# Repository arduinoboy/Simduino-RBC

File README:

Simduino RBC
-------------------
The object of this project is to create
a Arduino compatible robot controller using a minimum 
of parts.
-------------------
Bootloader
-------------------
The Simduino RBC uses the USBaspLoader
http://www.obdev.at/products/vusb/usbasploader.html
which uses a software only USB driver to connect to the 
computer without a FTDI chip.
note: it does not create a COM port,
instead it enumerates as a HID device
-------------------
Board
-------------------
The board is based off the metaboard
http://metalab.at/wiki/Metaboard
from MetaLab
http://metalab.at
A motor driver, sensor and servo connectors are also added 
-------------------

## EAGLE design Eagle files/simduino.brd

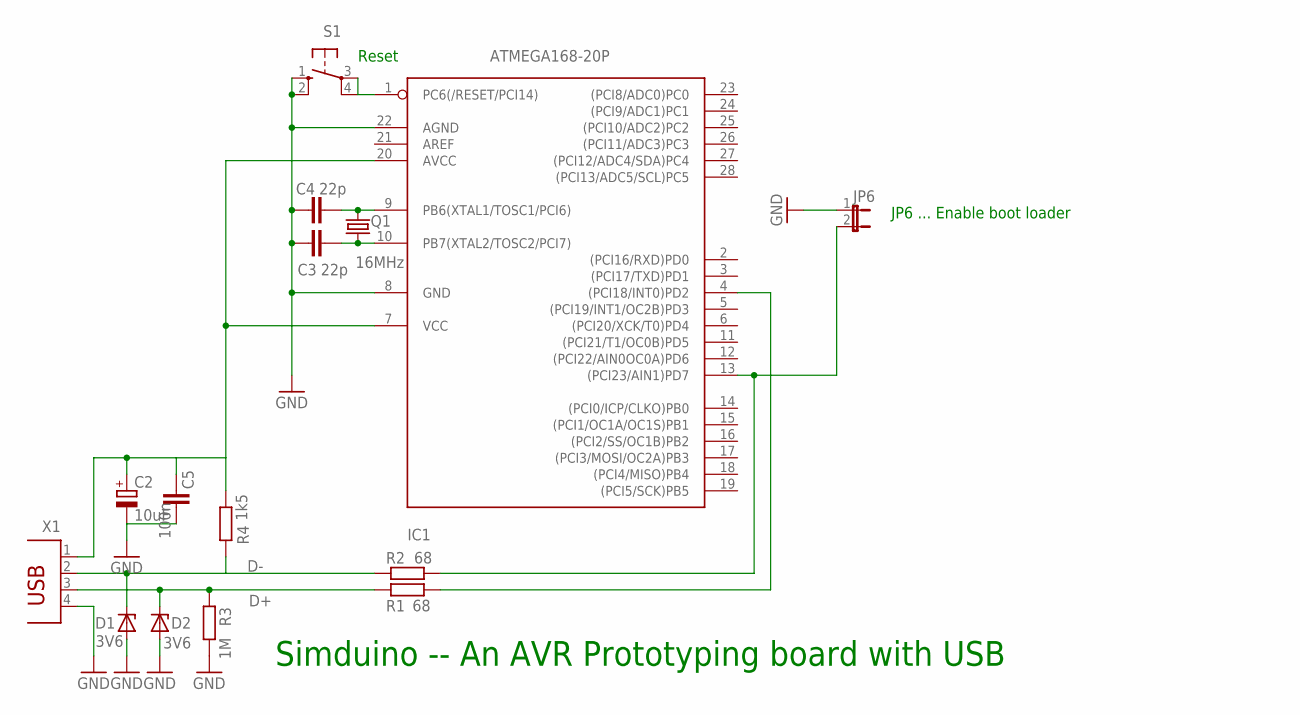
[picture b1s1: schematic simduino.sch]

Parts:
C2: 10uF; E2,5-6E
C3, C4: 22p; C025-024X044
C5: 100n; C025_050-025X075
D1, D2: 3V6; DO34Z7
IC1: ATMEGA168-20P; DIL28-3
JP6: JP1E; JP1
Q1: 16MHz; HC49/S
R1, R2: 68; 0207/10
R3: 1M; 0207/10
R4: 1k5; 0207/10
S1: 10-XX; B3F-10XX
X1: PN61729

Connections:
+5USB: C2.+, C5.1, IC1.7 (VCC), IC1.20 (AVCC), R4.1, X1.1
D+: D2.C, R1.1, R3.2, X1.3
D-: D1.C, R2.1, R4.2, X1.2
GND: C2.-, C3.1, C4.1, C5.2, D1.A, D2.A, IC1.8 (GND), IC1.22 (AGND), JP6.1, R3.1, S1.1 (S), S1.2 (S1), X1.4
unnamed: IC1.13 ((PCI23/AIN1)PD7), JP6.2, R2.2
unnamed: IC1.1 (PC6(/RESET/PCI14)), S1.3, S1.4 (P1)
unnamed: IC1.4 ((PCI18/INT0)PD2), R1.2
unnamed: C3.2, IC1.10 (PB7(XTAL2/TOSC2/PCI7)), Q1.1
unnamed: C4.2, IC1.9 (PB6(XTAL1/TOSC1/PCI6)), Q1.2

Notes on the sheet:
JP6 ... Enable boot loader
Simduino -- An AVR Prototyping board with USB
Reset

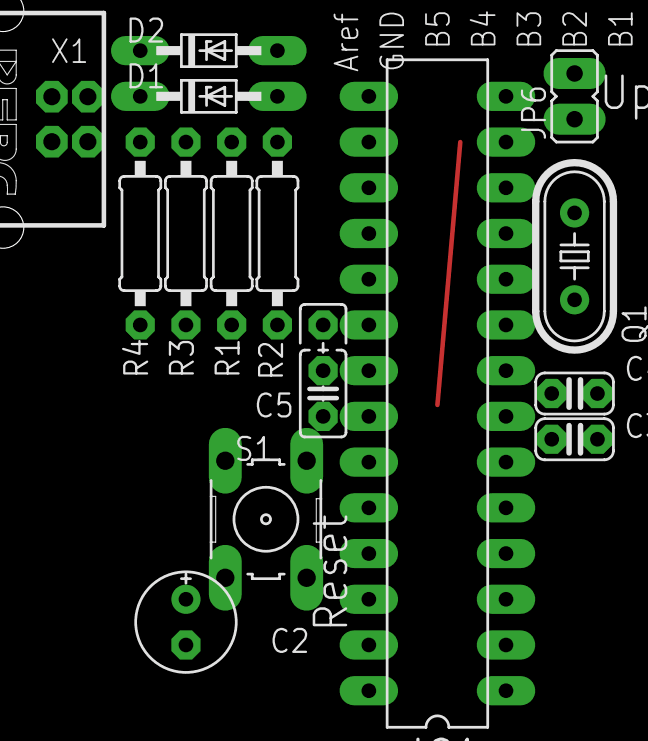
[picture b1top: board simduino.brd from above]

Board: 2 copper layers, 15 parts (0 on the bottom side), 9 nets.

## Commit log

2011-08-08 FIles! Warning the EAGLE CAD files are a copy of Simduino's, they are not finished!
2011-08-08 Terminal block instead of dc jack
2011-09-27 small stuff
2012-01-10 License added
    GPL
2012-01-10 clean up
2013-10-06 Stripping off extras
2013-10-06 Streamlining
2013-10-06 Cleanup
2013-10-06 Rerouting
